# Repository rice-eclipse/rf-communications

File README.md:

# NARWAL: Ground Station Radio for Rice Eclipse

This repo contains the work completed by Eclipse's RF Communications team during the 2022-2023 academic year.

Long-range Amplified Wireless Radio for Aerial Navigation (NARWAL) is Eclipse's first custom radio ground station. It was designed to interface with the Neutro iteration of Real-Time-Rocket (RTR), Eclipse's custom flight instruments package, and to receive telemetry data from RTR during flight.

The work completed by Eclipse's Flight Instruments team in developing RTR can be found [here](https://github.com/rice-eclipse/Real-Time-Rocket).

## NARWAL PCB

*TODO*

## NARWAL Code

*TODO*

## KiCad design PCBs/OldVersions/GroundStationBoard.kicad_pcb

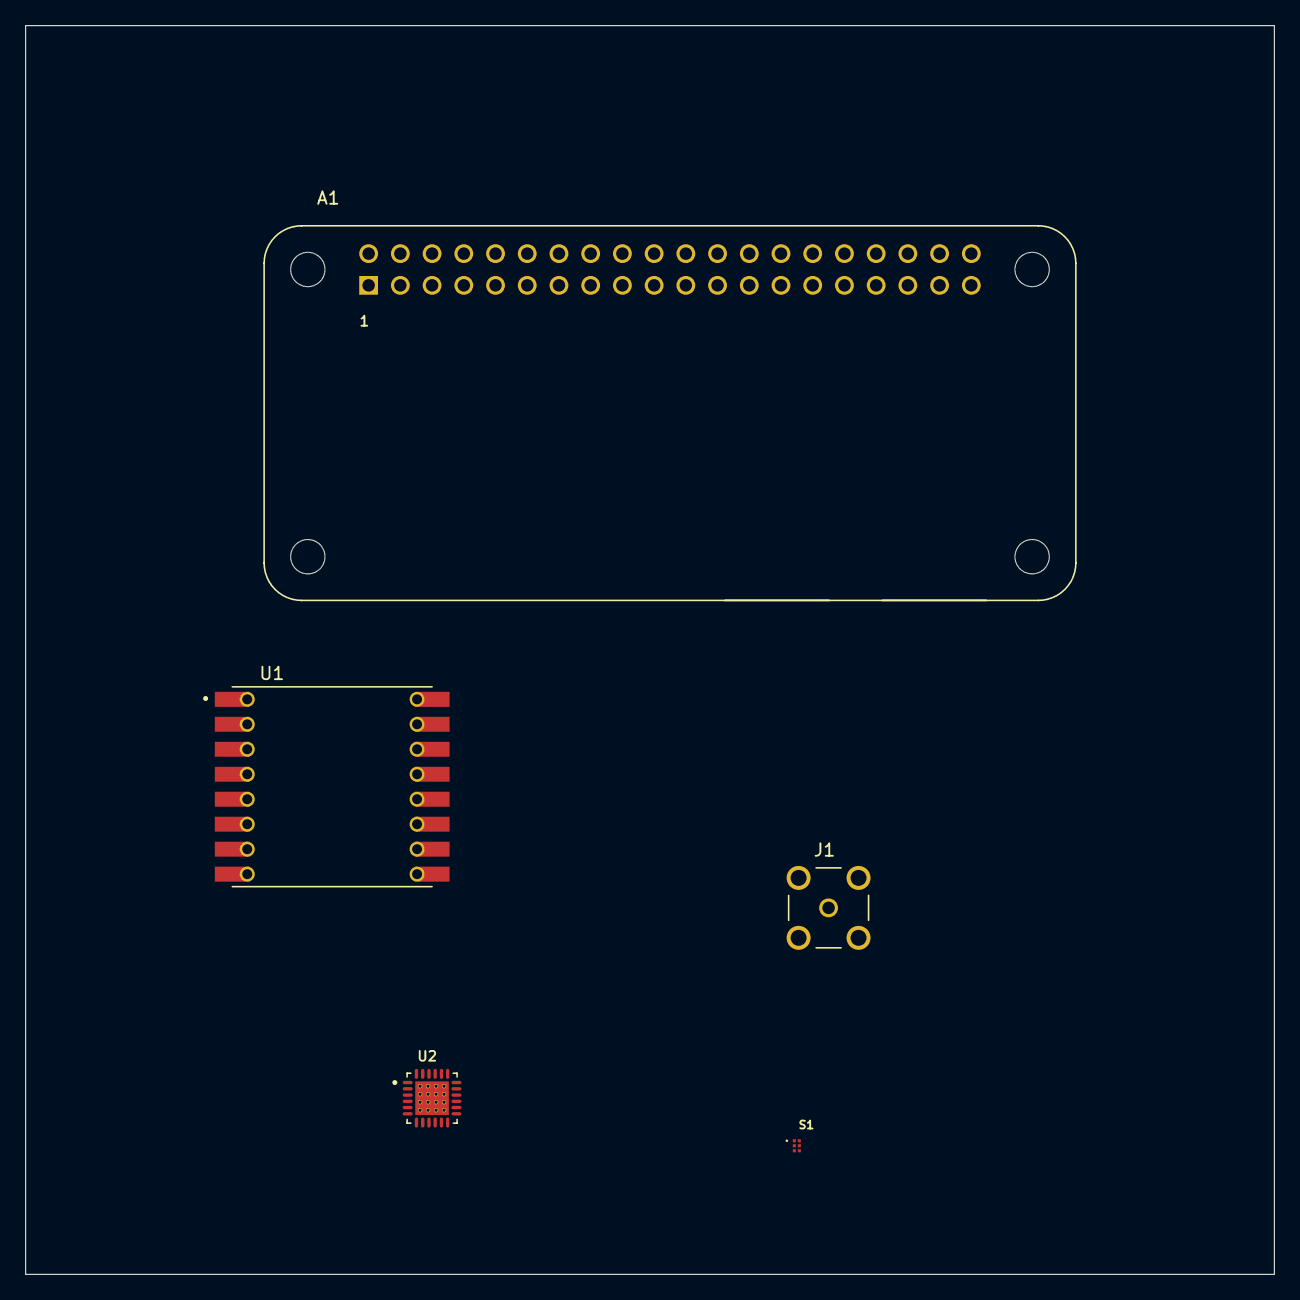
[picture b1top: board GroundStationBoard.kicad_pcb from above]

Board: 4 copper layers, 100.0 x 100.0 mm, 5 parts (0 on the bottom side), 21 nets, no tracks yet.

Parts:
A1: Raspberry Pi Zero; ADA3708_RPI-ZERO
J1: SMA_CONNECTOR; LPRS_SMA_CONNECTOR
S1: BGS12P2L6E6327XTSA1; SW_BGS12P2L6E6327XTSA1
U1: RFM98W; XCVR_RFM98W-433S2
U2: TQP7M9106; QFN50P400X400X90-25N

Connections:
+3.3V: A1.1 (3V3[1]), A1.17 (3V3[2]), S1.4 (VDD), U1.13 (3.3V)
+5V: A1.2 (5V[1]), A1.4 (5V[2])
ANT: J1.1, S1.3 (RF1)
CS: A1.24 (~CE0/GPIO8), U1.5 (NSS)
DIO0: A1.33 (GPIO13), U1.14 (DIO0)
DIO1: A1.35 (GPIO19), U1.15 (DIO1)
DIO2: A1.37 (GPIO26), U1.16 (DIO2)
DIO3: A1.36 (GPIO16), U1.11 (DIO3)
DIO4: A1.38 (GPIO20), U1.12 (DIO4)
DIO5: A1.40 (GPIO21), U1.7 (DIO5)
GND: A1.6 (GND[8]), A1.9 (GND[1]), A1.14 (GND[4]), A1.20 (GND[5]), A1.25 (GND[2]), A1.30 (GND[6]), A1.34 (GND[7]), A1.39 (GND[3]), J1.G1, J1.G2, J1.G3, J1.G4, S1.2 (GND), U1.1 (GND), U1.8 (GND), U1.10 (GND)
MISO: A1.21 (GPIO9/MISO), U1.2 (MISO)
MOSI: A1.19 (GPIO10/MOSI), U1.3 (MOSI)
unnamed: U2.4 (RF_IN), U2.5 (RF_IN)
unnamed: U2.2 (GND/NC), U2.3 (GND/NC), U2.6 (GND/NC), U2.7 (GND/NC), U2.8 (GND/NC), U2.9 (GND/NC), U2.10 (GND/NC), U2.11 (GND/NC), U2.12 (GND/NC), U2.13 (GND/NC), U2.17 (GND/NC), U2.19 (GND/NC), U2.20 (GND/NC), U2.21 (GND/NC), U2.22 (GND/NC), U2.23 (GND/NC), U2.24 (GND/NC)
unnamed: U2.14 (RF_OUT/VCC), U2.15 (RF_OUT/VCC), U2.16 (RF_OUT/VCC)
unnamed: U2.25 (RF/DC_GND), U2.26 (RF/DC_GND)
RF: S1.5 (RFIN), U1.9 (ANT)
RST: A1.11 (GPIO17/GEN0), U1.6 (RESET)
SCLK: A1.23 (GPIO11/SCLK), U1.4 (SCK)
SWCH: A1.13 (GPIO27/GEN2), S1.6 (CTRL)

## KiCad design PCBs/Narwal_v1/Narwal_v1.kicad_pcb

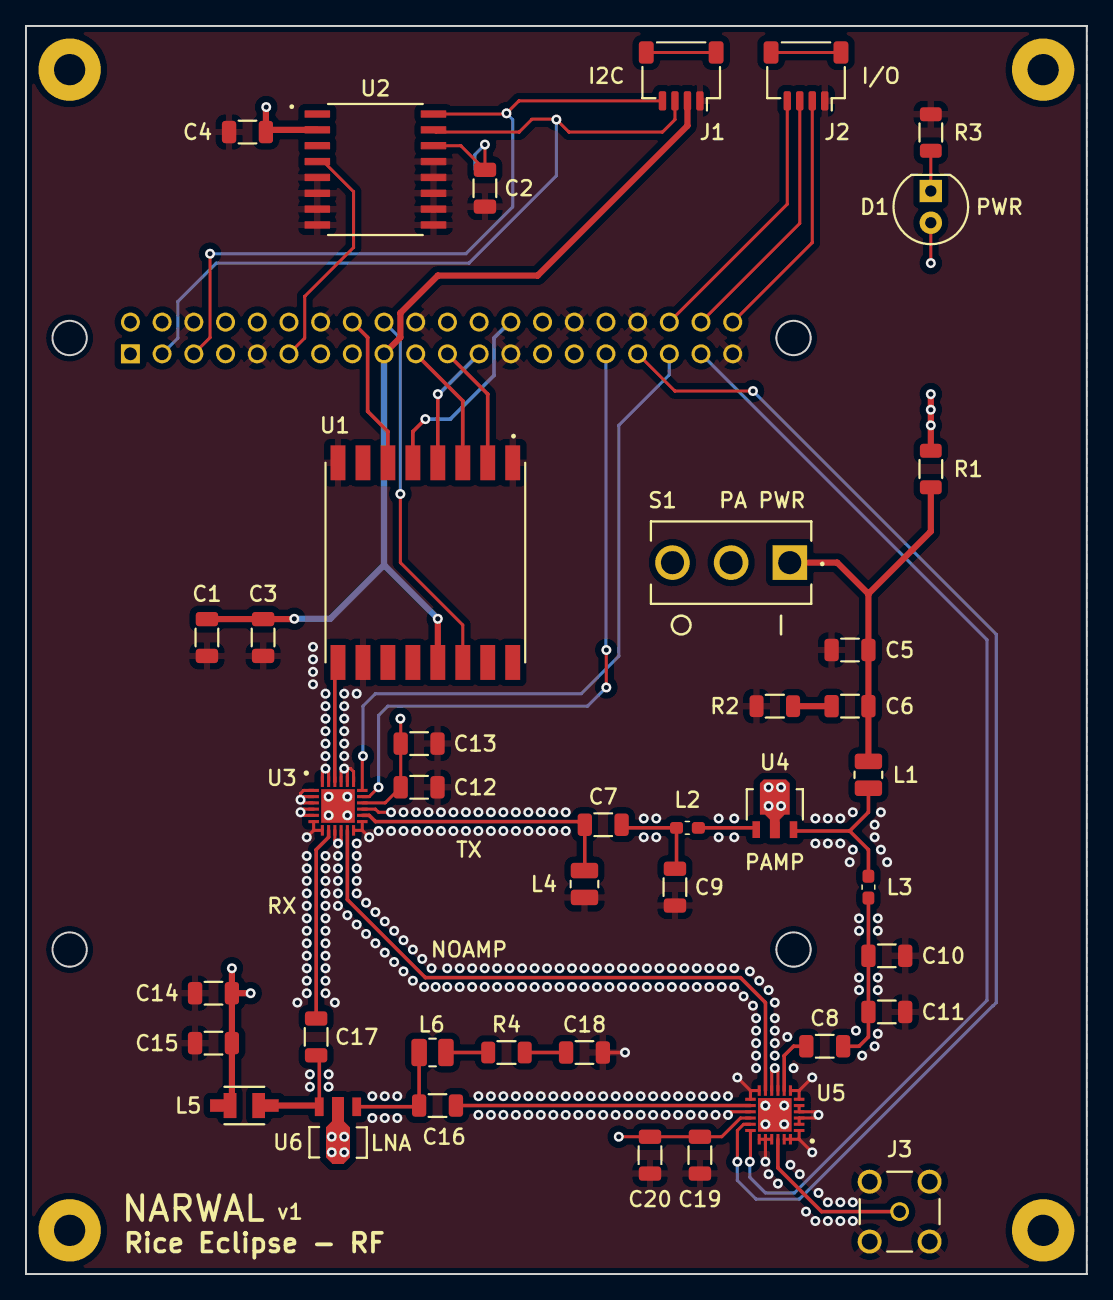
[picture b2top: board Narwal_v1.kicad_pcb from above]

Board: 4 copper layers, 85.0 x 100.0 mm, 47 parts (1 on the bottom side), 38 nets.

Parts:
A1: RASPBERRY-PI; RPI-4
BT1: S8411-45R; BATT-S8411-45R
C1, C13, C20: 1u; C_1206_3216Metric
C2, C3, C4: 100n; C_1206_3216Metric
C5: 2.2u; C_1206_3216Metric
C6, C12, C19: 100p; C_1206_3216Metric
C7: 12p; C_1206_3216Metric
C8: 39p; C_1206_3216Metric
C9: 15p; C_1206_3216Metric
C10, C11: 6.8p; C_1206_3216Metric
C14: 10u; C_1206_3216Metric
C15: 330n; C_1206_3216Metric
C16, C17: 10n; C_1206_3216Metric
C18: 330p; C_1206_3216Metric
D1: PWR; LED_D5.0mm
H1, H2, H3, H4: MountingHole_Pad; MountingHole_2.5mm_Pad
J1, J2: JST-SH; JST_SH_SM04B-SRSS-TB_1x04-1MP_P1.00mm_Horizontal
J3: SMA-LPRS; SMA-LPRS-CONNECTOR
L1: 47n; L_1008_2520Metric
L2: 4.3n; L_0603_1608Metric_Pad1.05x0.95mm_HandSolder
L3: 5.1n; L_0603_1608Metric_Pad1.05x0.95mm_HandSolder
L4: 40n; L_1008_2520Metric
L5: LQH32NH4R7J23L; CHOKE-LQH32NH4R7J23L
L6: 620n; L_1008_2520Metric
R1: 0R; R_1206_3216Metric
R2: 5.1R; R_1206_3216Metric
R3: 1K; R_1206_3216Metric
R4: 150R; R_1206_3216Metric
S1: 500SSP1S1M2QEA; SWITCH-500SSP1S1M2QEA
U1: RFM96W-433; TRX-RFM98W-433
U2: DS3231M; RTC-DS3231M-TRL
U3, U5: HSWA4-63DR+; SWITCH-HSWA4-63DR+
U4: HMC452ST89; PAMP-HMC453ST89ETR
U6: PGA-103+; LNA-PGA-103+

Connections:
+3.3V: A1.17 (3V3[2]), C1.2, C3.2, J1.2, U1.13 (3.3V)
+5V: A1.2 (5V[1]), A1.4 (5V[2]), C4.2, C12.1, C13.1, C14.1, C15.1, C19.1, C20.1, D1.2 (A), L5.1, R1.1, S1.2, U2.2 (VCC), U3.16 (VDD), U5.16 (VDD)
BUT1: A1.36 (GPIO16), J2.4
BUT2: A1.38 (GPIO20), J2.3
BUT3: A1.40 (GPIO21), J2.2
CS: A1.26 (~CE1/GPIO7), U1.5 (NSS)
CTRL1A: A1.31 (GPIO6), U3.17 (CONTROL_1)
CTRL1B: A1.33 (GPIO13), U5.17 (CONTROL_1)
CTRL2A: A1.35 (GPIO19), U3.18 (CONTROL_2)
CTRL2B: A1.37 (GPIO26), U5.18 (CONTROL_2)
DIO0: A1.18 (GEN5/GPIO24), U1.14 (DIO0)
GND: A1.6 (GND[8]), A1.9 (GND[1]), A1.14 (GND[4]), A1.20 (GND[5]), A1.25 (GND[2]), A1.30 (GND[6]), A1.34 (GND[7]), A1.39 (GND[3]), BT1.N, C1.1, C2.2, C3.1, C4.1, C5.2, C9.2, C10.2, C11.2, C12.2, C13.2, C14.2, C15.2, C18.2, C19.2, C20.2, J1.1, J2.1, J3.G1, J3.G2, J3.G3, J3.G4, L4.2, R2.2, R3.2, U1.1 (GND), U1.8 (GND), U1.10 (GND), U2.5 (GND), U2.6 (GND), U2.7 (GND), U2.8 (GND), U2.9 (GND), U2.10 (GND), U2.11 (GND), U2.12 (GND), U2.13 (GND), U3.1 (GND_1), U3.2 (GND_2), U3.3 (GND_3), U3.4 (GND_4), U3.5 (RF4), U3.6 (GND_5), U3.7 (GND_6), U3.9 (GND_7), U3.10 (GND_8), U3.12 (GND_9), U3.13 (GND_10), U3.15 (GND_11), U3.19 (CONTROL_3), U3.20 (GND_12), U3.21 (GND_13), U3.23 (GND_14), U3.24 (GND_15), U3.25 (PADDLE), U4.2 (GND), U5.1 (GND_1), U5.2 (GND_2), U5.3 (GND_3), U5.4 (GND_4), U5.5 (RF4), U5.6 (GND_5), U5.7 (GND_6), U5.9 (GND_7), U5.10 (GND_8), U5.12 (GND_9), U5.13 (GND_10), U5.15 (GND_11), U5.19 (CONTROL_3), U5.20 (GND_12), U5.21 (GND_13), U5.23 (GND_14), U5.24 (GND_15), U5.25 (PADDLE), U6.2 (GND)
LNA-ANT: C16.1, U5.14 (RF1)
LNA-TRX: C17.2, U3.8 (RF3)
MISO: A1.21 (GPIO9/MISO), U1.2 (MISO)
MOSI: A1.19 (GPIO10/MOSI), U1.3 (MOSI)
NOAMP: U3.11 (RF2), U5.11 (RF2)
unnamed: BT1.P, C2.1, U2.14 (VBAT)
unnamed: C5.1, C6.1, L1.1, R1.2, S1.1
unnamed: C6.2, R2.1
unnamed: C7.2, C9.1, L2.1
unnamed: C8.1, C10.1, C11.1, L3.2
unnamed: C16.2, L6.1, U6.1
unnamed: C17.1, L5.2, U6.3
unnamed: C18.1, R4.2
unnamed: D1.1 (K), R3.1
unnamed: J3.1, U5.22 (RF_COM)
unnamed: L1.2, L3.1, U4.3
unnamed: L2.2, U4.1
unnamed: L6.2, R4.1
PAMP-ANT: C8.2, U5.8 (RF3)
PAMP-TRX: C7.1, L4.1, U3.14 (RF1)
RST-RTC: A1.11 (GPIO17/GEN0), U2.4 (~RST)
RST-TRX: A1.16 (GEN4/GPIO23), U1.6 (RESET)
SCL: A1.5 (GPIO3/SCL), J1.4, U2.16 (SCL)
SCLK: A1.23 (GPIO11/SCLK), U1.4 (SCK)
SDA: A1.3 (GPIO2/SDA), J1.3, U2.15 (SDA)
TRX: U1.9 (ANT), U3.22 (RF_COM)

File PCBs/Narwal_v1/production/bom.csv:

Designator,Footprint,Quantity,Value,LCSC Part #
A1,RPI-4,1,RASPBERRY-PI,
BT1,BATT-S8411-45R,1,S8411-45R,
"C1, C13, C20",C_1206_3216Metric,3,1u,
"C10, C11",C_1206_3216Metric,2,6.8p,
"C12, C19, C6",C_1206_3216Metric,3,100p,
C14,C_1206_3216Metric,1,10u,
C15,C_1206_3216Metric,1,330n,
"C16, C17",C_1206_3216Metric,2,10n,
C18,C_1206_3216Metric,1,330p,
"C2, C3, C4",C_1206_3216Metric,3,100n,
C5,C_1206_3216Metric,1,2.2u,
C7,C_1206_3216Metric,1,12p,
C8,C_1206_3216Metric,1,39p,
C9,C_1206_3216Metric,1,15p,
D1,LED_D3.0mm,1,LED,
"H1, H2, H3, H4",MountingHole_2.5mm_Pad,4,MountingHole_Pad,
"J1, J2",JST_SH_SM04B-SRSS-TB_1x04-1MP_P1.00mm_Horizontal,2,JST-SH,
J3,SMA-LPRS-CONNECTOR,1,SMA-LPRS,
L1,L_1008_2520Metric,1,47n,
L2,L_1210_3225Metric,1,4.3n,
L3,L_1210_3225Metric,1,5.1n,
L4,L_1008_2520Metric,1,40n,
L5,CHOKE-LQH32NH4R7J23L,1,LQH32NH4R7J23L,
L6,L_1008_2520Metric,1,620n,
R1,R_1206_3216Metric,1,47K,
R2,R_1206_3216Metric,1,0R,
R3,R_1206_3216Metric,1,5.1R,
R4,R_1206_3216Metric,1,1K,
R5,R_1206_3216Metric,1,150R,
S1,SWITCH-500SSP1S1M2QEA,1,500SSP1S1M2QEA,
U1,TRX-RFM98W-433,1,RFM96W-433,
U2,RTC-DS3231M-TRL,1,DS3231M,
"U3, U5",SWITCH-HSWA4-63DR+,2,HSWA4-63DR+,
U4,PAMP-HMC453ST89ETR,1,HMC452ST89,
U6,LNA-PGA-103+,1,PGA-103+,

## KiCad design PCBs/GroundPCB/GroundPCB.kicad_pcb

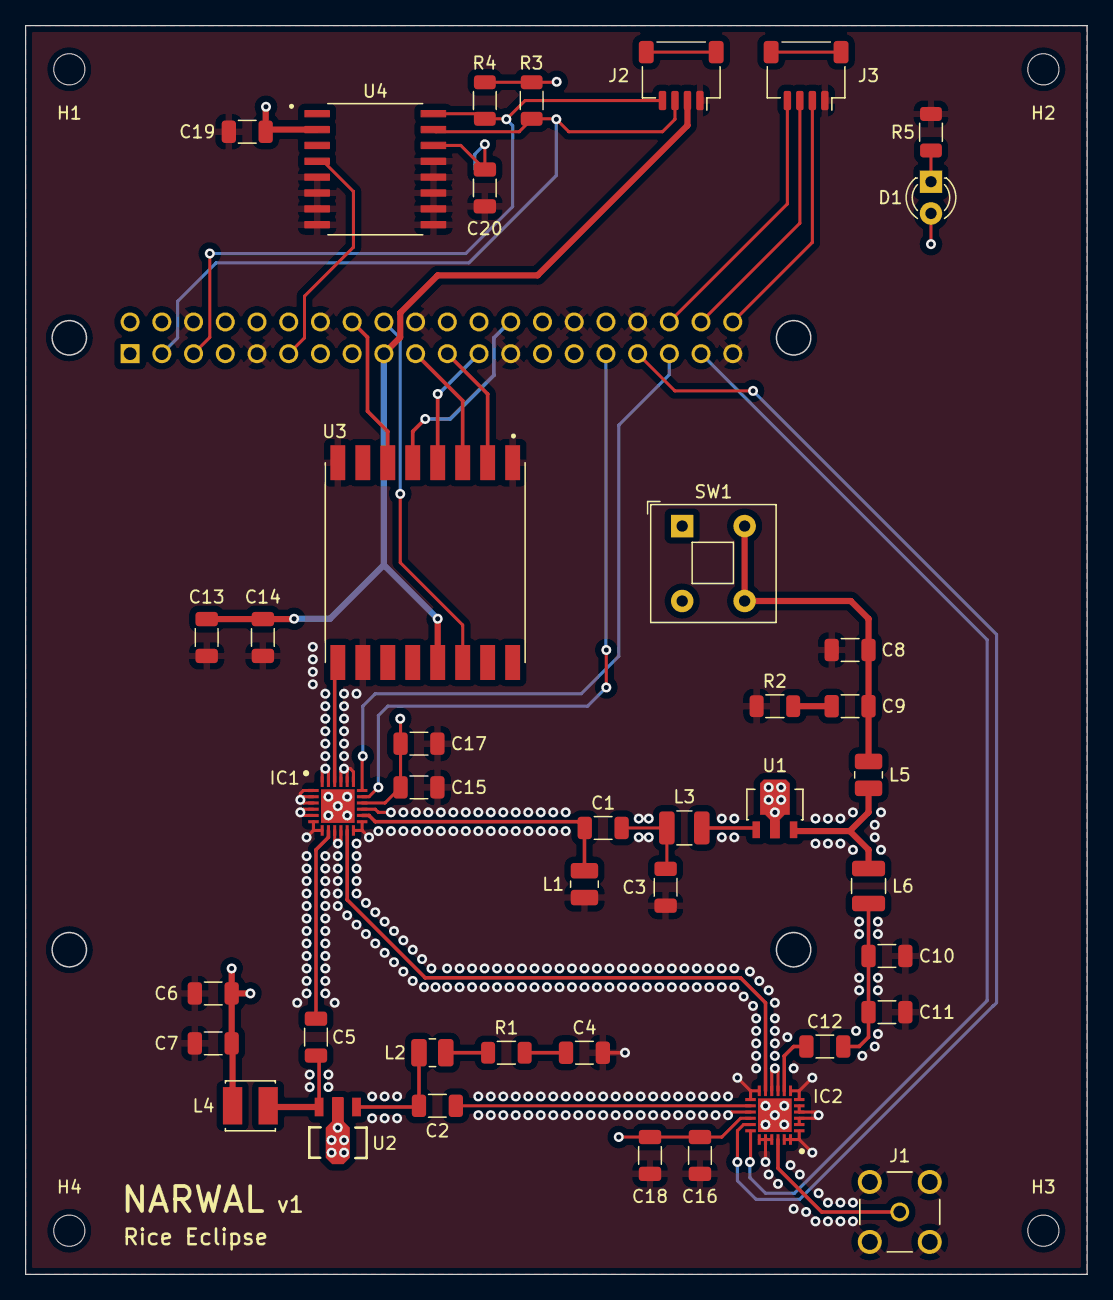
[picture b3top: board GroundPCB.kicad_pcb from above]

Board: 4 copper layers, 85.0 x 100.0 mm, 48 parts (1 on the bottom side), 38 nets.

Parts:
A1: RPI-ZERO-ADA3708; RPI-4
BT1: BATT-S8411-45R
C1: 12p; C_1206_3216Metric
C2, C5: 10n; C_1206_3216Metric
C3: 15p; C_1206_3216Metric
C4: 330p; C_1206_3216Metric
C6: 10u; C_1206_3216Metric
C7: 330n; C_1206_3216Metric
C8: 2.2u; C_1206_3216Metric
C9: 100p; C_1206_3216Metric
C10, C11: 6.8p; C_1206_3216Metric
C12: 39p; C_1206_3216Metric
C13, C17, C18: 1u; C_1206_3216Metric
C14, C15, C16, C19, C20: 100n; C_1206_3216Metric
D1: LED; LED_D3.0mm
H1, H2, H3, H4: MountingHole; MountingHole_2.5mm
IC1, IC2: SWITCH-HSWA4-63DR+
J1: SMA-LPRS-CONNECTOR
J2, J3: Conn_01x04; JST_SH_SM04B-SRSS-TB_1x04-1MP_P1.00mm_Horizontal
L1: 40n; L_1008_2520Metric
L2: 620n; L_1008_2520Metric
L3: 4.3n; L_1210_3225Metric
L4: CHOKE-LQH44PN4R7MP0L
L5: 47n; L_1008_2520Metric
L6: 5.1n; L_1210_3225Metric
R1: 150R; R_1206_3216Metric
R2: 5.1R; R_1206_3216Metric
R3, R4: 4.7K; R_1206_3216Metric
R5: 154R; R_1206_3216Metric
SW1: SW_SPST; SW_Push_2P1T_Toggle_CK_PVA1xxH1xxxxxxV2
U1: HMC452ST89ETR; PAMP-HMC453ST89ETR
U2: PGA-103+; LNA-PGA-103+
U3: RFM96W-433S2; TRX-RFM98W-433
U4: DS3231M; RTC-DS3231M-TRL

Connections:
+3.3V: A1.17 (3V3[2]), C13.2, C14.2, J2.2, U3.13 (3.3V)
+5V: A1.2 (5V[1]), A1.4 (5V[2]), C6.1, C7.1, C15.1, C16.1, C17.1, C18.1, C19.2, D1.2 (A), IC1.16 (VDD), IC2.16 (VDD), L4.1, R3.1, R4.1, SW1.1 (A), SW1.3 (A), U4.2 (VCC)
BUT1: A1.36 (GPIO16), J3.4
BUT2: A1.38 (GPIO20), J3.3
BUT3: A1.40 (GPIO21), J3.2
CS: A1.26 (~CE1/GPIO7), U3.5 (NSS)
CTRL1A: A1.31 (GPIO6), IC1.17 (CONTROL_1)
CTRL1B: A1.33 (GPIO13), IC2.17 (CONTROL_1)
CTRL2A: A1.35 (GPIO19), IC1.18 (CONTROL_2)
CTRL2B: A1.37 (GPIO26), IC2.18 (CONTROL_2)
DIO0: A1.18 (GEN5/GPIO24), U3.14 (DIO0)
GND: A1.6 (GND[8]), A1.9 (GND[1]), A1.14 (GND[4]), A1.20 (GND[5]), A1.25 (GND[2]), A1.30 (GND[6]), A1.34 (GND[7]), A1.39 (GND[3]), BT1.N, C3.2, C4.2, C6.2, C7.2, C8.2, C10.2, C11.2, C13.1, C14.1, C15.2, C16.2, C17.2, C18.2, C19.1, C20.2, IC1.1 (GND_1), IC1.2 (GND_2), IC1.3 (GND_3), IC1.4 (GND_4), IC1.5 (RF4), IC1.6 (GND_5), IC1.7 (GND_6), IC1.9 (GND_7), IC1.10 (GND_8), IC1.12 (GND_9), IC1.13 (GND_10), IC1.15 (GND_11), IC1.19 (CONTROL_3), IC1.20 (GND_12), IC1.21 (GND_13), IC1.23 (GND_14), IC1.24 (GND_15), IC1.25 (PADDLE), IC2.1 (GND_1), IC2.2 (GND_2), IC2.3 (GND_3), IC2.4 (GND_4), IC2.5 (RF4), IC2.6 (GND_5), IC2.7 (GND_6), IC2.9 (GND_7), IC2.10 (GND_8), IC2.12 (GND_9), IC2.13 (GND_10), IC2.15 (GND_11), IC2.19 (CONTROL_3), IC2.20 (GND_12), IC2.21 (GND_13), IC2.23 (GND_14), IC2.24 (GND_15), IC2.25 (PADDLE), J1.G1, J1.G2, J1.G3, J1.G4, J2.1, J3.1, L1.2, R2.2, R5.2, U1.2 (GND), U2.2 (GND), U3.1 (GND), U3.8 (GND), U3.10 (GND), U4.5 (GND), U4.6 (GND), U4.7 (GND), U4.8 (GND), U4.9 (GND), U4.10 (GND), U4.11 (GND), U4.12 (GND), U4.13 (GND)
LNA-ANT: C2.1, IC2.14 (RF1)
LNA-TRX: C5.2, IC1.8 (RF3)
MISO: A1.21 (GPIO9/MISO), U3.2 (MISO)
MOSI: A1.19 (GPIO10/MOSI), U3.3 (MOSI)
NOAMP: IC1.11 (RF2), IC2.11 (RF2)
unnamed: BT1.P, C20.1, U4.14 (VBAT)
unnamed: C1.2, C3.1, L3.1
unnamed: C2.2, L2.1, U2.1
unnamed: C4.1, R1.2
unnamed: C5.1, L4.2, U2.3
unnamed: C8.1, C9.1, L5.1, SW1.2 (B), SW1.4 (B)
unnamed: C9.2, R2.1
unnamed: C10.1, C11.1, C12.1, L6.2
unnamed: D1.1 (K), R5.1
unnamed: IC2.22 (RF_COM), J1.1
unnamed: L2.2, R1.1
unnamed: L3.2, U1.1
unnamed: L5.2, L6.1, U1.3
PAMP-ANT: C12.2, IC2.8 (RF3)
PAMP-TRX: C1.1, IC1.14 (RF1), L1.1
RST-RTC: A1.11 (GPIO17/GEN0), U4.4 (~RST)
RST-TRX: A1.16 (GEN4/GPIO23), U3.6 (RESET)
SCL: A1.5 (GPIO3/SCL), J2.4, R4.2, U4.16 (SCL)
SCLK: A1.23 (GPIO11/SCLK), U3.4 (SCK)
SDA: A1.3 (GPIO2/SDA), J2.3, R3.2, U4.15 (SDA)
TRX: IC1.22 (RF_COM), U3.9 (ANT)

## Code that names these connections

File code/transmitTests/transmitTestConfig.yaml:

frequency_mhz: 433.0
cs_pin: CE1
reset_pin: D25
ctrl1A_pin: D6
ctrl2A_pin: D19
ctrl1B_pin: D13
ctrl2B_pin: D26
enable_bypass: False
enable_amps: True
packets_per_transmit: 1
transmit_per_second: 0.25
callsign: CLSIGN
data_types:
  - send_time: q
  - ping_time: q
  - bandwidth: i
  - spreading: h
  - tx_power: h
  - test_num: H
  - orig_rssi: d
  - orig_snr: d

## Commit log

2022-09-07 add description to readme
2022-09-07 create Code and PCBs folders
2022-09-15 This is a Pi Zero W schematic&&footprint commit
2022-09-15 This is a 2nd Pi Zero W schematic&&footprint commit
2022-09-18 added RFM98W transceiver symbol & footprint
2022-09-22 created pcb file
2022-09-22 added footprint for switch
2022-09-22 4 layer-ifying the PCB, traces, board cuts and trace width
2022-09-27 added SMA connector and RF switch to schematic
2022-09-27 worked on data I/O pins
2022-09-29 added amplifier
2022-09-29 decoupling capacitors & amplifier
2022-10-02 started code
2022-10-06 Update Transmit.py
    Examined the code and re-wrote a little bit. Next steps: look at the bitrate budget file and format a message to include all necessary data
2022-10-07 Update Transmit.py
    Added a function, send_to_ground(), that builds a message from a yaml file.
2022-10-16 I/O for yaml file
2022-10-16 Changed the format from 4 tabs of indentation to 4 spaces in the yaml file
2022-10-20 Changed send_to_ground() to be send() and made it take arguments instead of reading from a file. Also turned Transmit into a class
2022-10-22 Changed Transmit.py back to a simple script and created a new, unified Radio class that can handle sending and receiving with only one rfm9x instance.
2022-10-23 last config
2022-10-23 Radio now sends data as Floats instead of Integers. Also renamed send_data() to send_flight_data() and added reformat_received_data() to aid in getting flight data
2022-10-23 "recieved" --> "received"
2022-10-23 Current code from Carter
2022-10-23 syncing
2022-10-23 Added a docstring
2022-10-23 Added methods in Radio to help in testing.
2022-10-27 Change branch?
2022-10-27 Fixed a small issue in Radio's receive function
2022-10-27 Test cases now sends bursts of 10 packets per case, to ensure reception. Added a number of comments and helpful messages for future reference.
2022-10-27 Making sure everything is updated. Also added a link to a blog article that has a nice description of floating point precision.
2022-10-30 Changed Radio to implement config files!
2022-10-31 Adding example config file; This will be used for testing
2022-11-01 Deleted some debugging code that was still hanging around Also fiddled with the data types of values in testconfig.yaml
2022-11-06 Deleted unused / superseded code like Transmit.py and Receive.py (replaced by Radio.py)
2022-11-06 Created receive_and_write.py to receive packets from test_cases.py, and created a pair of scripts to ping packets back and forth for more accurate time measurements
2022-11-07 pre-revision backup
2022-11-08 connectors, switch, test points
2022-11-10 Began working on data visualization and created temporary dummy log.tsv for testing
2022-11-14 initial layout changes
2022-11-14 relocated components, added switch to layout
2022-11-14 data_grapher.py should now work as intended. We'll see if we get any issues once we actually have data to graph!
2022-11-21 post-review revisions
2022-11-21 name change and readme
2022-12-08 power switch fixes, JLC compatibility changes
2022-12-08 JLC-required silkscreen changes
2022-12-13 final changes and fabrication
2023-01-13 Ensuring github is all up-to-date
2023-01-13 Re-organized to make it clear which files need to go on the pi right now. Created piTestSend.py and piTestReceive.py and pitestconfig.yaml to make sure that the Radio class is actually working on the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
2023-01-13 Added one (1) comma to piTestSend.py
2023-01-13 Created new transmissionTest files that should actually work with how RFM9X/LoRa works. Cautiously optimistic that they might work. Also relocated Radio.py to its own directory for organizational pur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
2023-01-13 Pycharm saw what I was doing and was like, "You are an idiot, let me do that for you" and it was right
2023-01-13 Moved the piTest scripts to their own directory for organization
2023-01-13 Pycharm lied
2023-01-13 Pins moved to config, Error with loading config fixed
2023-01-13 Renamed piTestConfig to make it more consistent
2023-01-13 The piTests can now properly locate Radio.py (I hope)
2023-01-13 Now Radio actually updates RFM9X when loading a config
2023-01-13 Radio no longer creates an RFM9X without a configuration loaded
2023-01-13 Radio *does* need to create SPI in init though
2023-01-13 Capitalize T and C
2023-01-13 Now order is types
2023-01-13 Listify dict_values object
2023-01-13 Honestly don't remember what I just fixed lol
2023-01-13 Radio Receive unpacking data fixed
2023-01-13 Fixed struct unpacking
2023-01-18 Fixed Key Error in transmissionTestReceive.py
2023-01-18 transmissionTestSend.py and transmissionTestReceive.py now print the radio configuration
2023-01-18 Send now prints ack_pack
2023-01-18 Send and Receive now print the packet (or None) that they've received
2023-01-18 Added plenty of debug prints
2023-01-18 Debug print
2023-01-20 print update
2023-01-20 increased wait time
2023-01-20 fixed ping
2023-01-20 added skip test after 3 failures
2023-01-20 fixed skip test after 3 failures
2023-01-20 now skips after 3 failures
2023-01-20 less tests
2023-01-20 synced?
2023-01-20 typo
2023-01-20 typo2
2023-01-20 small fix
2023-01-21 Properly sync tests
2023-01-21 Radio now loads a configuration in its constructor
2023-01-22 test commit
2023-01-22 Log file (log.yaml now) is updated immediately after each test, so data will not be lost in the event of a fatal error
2023-01-22 Added a few comments, reorganized transmissionTestReceive.py so that updating the radio config is a unique function, since the same code is reused multiple times
2023-01-22 print changes
2023-01-22 logic error
2023-01-22 resync when reconnected
2023-01-22 Rewrote data_grapher.py into visualizer.py, which is more general and should work with yaml-type data
2023-01-22 visualizer.py now has axes title that explains color
2023-01-22 Final time is now the second time of flight, like ping time
2023-01-23 cleaning up branch part 1
2023-01-23 cleanup branch
2023-01-23 removal
2023-01-23 add back
2023-01-23 adding back renamed
2023-01-23 deleted empty folders
2023-01-23 cleanup
2023-01-23 restoring readme
2023-01-25 changed timeout from 4 to 8 seconds
2023-01-25 Adding data from first test, testlog.yaml
2023-01-25 visualizer.py can now handle 2, 3, and (technically) 4 dimensional graphs! I have been advised not to add more dimensions!
2023-01-25 I will add more dimensions.
2023-02-19 Took fieldlog.yaml from Pi. It's the test when we were out in the field before we had NARWAL
2023-02-19 Added NARWAL RF switch support to Radio.py and swapped spreading factor and bandwidth in transmitTestSend.py and transmitTestReceive.py so that the longer tests will be later on
2023-02-19 Committed recivee
2023-02-19 Swapped the order of the bandwidths to move high SF and low bandwidth to the end of the tests
2023-02-19 Added enable_amps to enable the RF switch control for NARWAL
2023-02-25 this is dumb
2023-02-25 Actually getting the pin from the board now in Radio
2023-02-26 Fixed two typos in Radio that probably made the test not work 💀
2023-02-26 Swapped orig_snr and orig_rssi because they were backwards
2023-02-26 Swapped orig_snr and orig_rssi back so they should be correct now
2023-02-26 Fixed RF Switch switching; "1A" goes with "2A" and "1B" goes with "2B", not the other way around
2023-02-26 Added timestamps at key points in radio.send and radio.receive for debugging
2023-02-26 Added comment; why aren't my commits working??
2023-02-26 Added a 0.5 second pause between sending and receiving (is that how you spell receiving?)
2023-02-26 narwal is sleepy
2023-02-26 Github??
2023-02-26 Added a short delay after receiving in transmitTestSend.py
2023-03-14 started launch test code
2023-03-22 launch test codebase! pog
2023-03-22 launch test code example
2023-03-22 Wrote code of dubious quality to sync the system's time with the RTC and sync the RTC with the system's time
2023-04-02 Reorganized the RTC code into a new class, RTC, which will handle keeping the system up-to-date.
2023-05-05 lots of changes
2023-05-05 reorganized logs
2023-05-05 created modified version of rfm9x module
2023-05-05 testing modified module
2023-05-11 readme update
2023-05-11 started writing FSK library
2023-06-16 FSK library progress
2023-06-17 finished FSK library implementation
2023-06-17 renamed FSK library
2023-06-17 file restructuring
2023-06-19 wrote FSK radio wrapper class and config file
2023-06-19 reorganized module files
2023-06-19 created Narwal and RTR config files
2023-06-19 bugfixing
2023-06-19 wrote PATH insertion script
2023-06-20 command-sending
2023-06-20 bugfixes
2023-06-21 gps script
2023-06-21 code reorganization
2023-06-21 finished sensor code
2023-06-21 adding basic altimeter functionality
2023-06-21 progressgit add -A
2023-06-21 more stuff
2023-06-21 deleted gps.py
2023-06-21 more changes
2023-06-22 save
2023-06-22 save code from narwal
2023-06-22 logging on narwal
